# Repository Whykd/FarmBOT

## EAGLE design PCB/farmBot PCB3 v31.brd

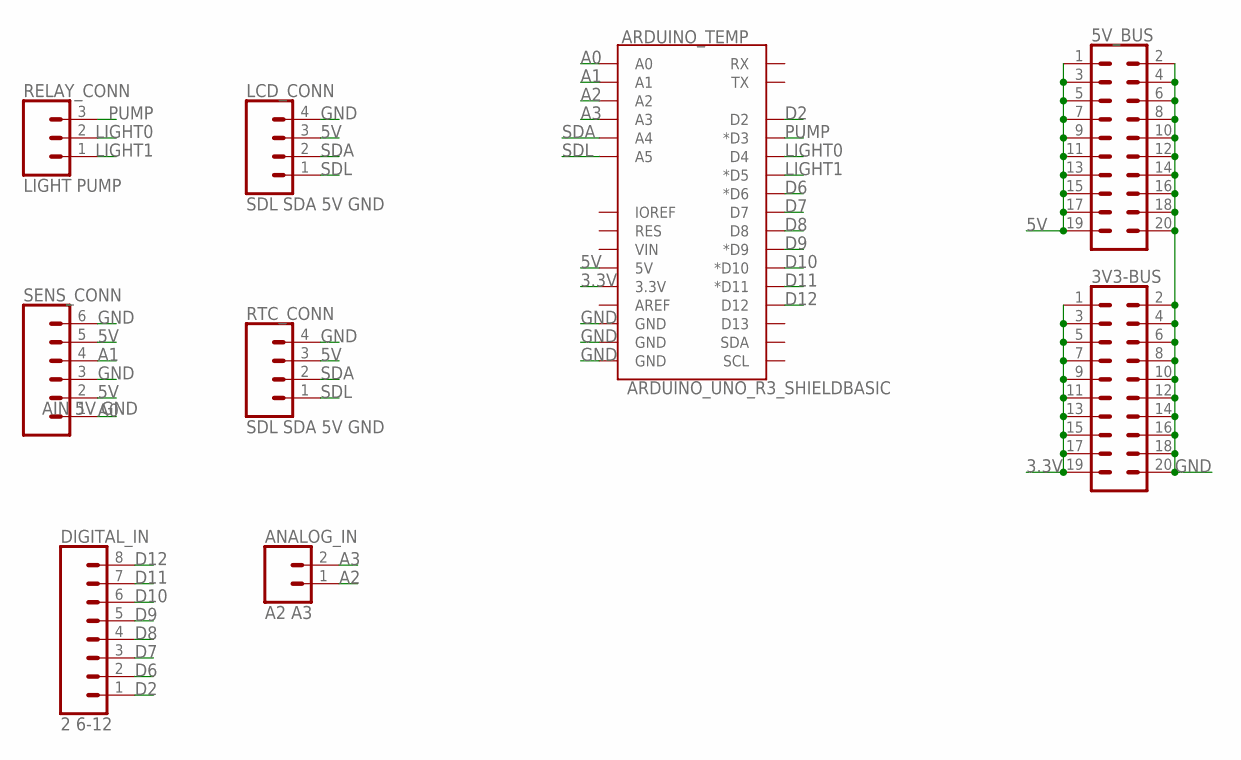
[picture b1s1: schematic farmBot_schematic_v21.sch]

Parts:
3V3-BUS, 5V_BUS: CONN_10X2; 2X10
ANALOG_IN: A2 A3; 1X02
ARDUINO_TEMP: ARDUINO_UNO_R3_SHIELDBASIC; UNO_R3_SHIELD
DIGITAL_IN: 2 6-12; 1X08
LCD_CONN: SDL SDA 5V GND; 1X04
RELAY_CONN: LIGHT PUMP; 1X03
RTC_CONN: SDL SDA 5V GND; 1X04
SENS_CONN: AIN 5V GND; 1X06

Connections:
3.3V: 3V3-BUS.1, 3V3-BUS.3, 3V3-BUS.5, 3V3-BUS.7, 3V3-BUS.9, 3V3-BUS.11, 3V3-BUS.13, 3V3-BUS.15, 3V3-BUS.17, 3V3-BUS.19, ARDUINO_TEMP.3.3V
5V: 5V_BUS.1, 5V_BUS.3, 5V_BUS.5, 5V_BUS.7, 5V_BUS.9, 5V_BUS.11, 5V_BUS.13, 5V_BUS.15, 5V_BUS.17, 5V_BUS.19, ARDUINO_TEMP.5V, LCD_CONN.3, RTC_CONN.3, SENS_CONN.2, SENS_CONN.5
A0: ARDUINO_TEMP.A0, SENS_CONN.1
A1: ARDUINO_TEMP.A1, SENS_CONN.4
A2: ANALOG_IN.1, ARDUINO_TEMP.A2
A3: ANALOG_IN.2, ARDUINO_TEMP.A3
D2: ARDUINO_TEMP.D2, DIGITAL_IN.1
D6: ARDUINO_TEMP.D6 (*D6), DIGITAL_IN.2
D7: ARDUINO_TEMP.D7, DIGITAL_IN.3
D8: ARDUINO_TEMP.D8, DIGITAL_IN.4
D9: ARDUINO_TEMP.D9 (*D9), DIGITAL_IN.5
D10: ARDUINO_TEMP.D10 (*D10), DIGITAL_IN.6
D11: ARDUINO_TEMP.D11 (*D11), DIGITAL_IN.7
D12: ARDUINO_TEMP.D12, DIGITAL_IN.8
GND: 3V3-BUS.2, 3V3-BUS.4, 3V3-BUS.6, 3V3-BUS.8, 3V3-BUS.10, 3V3-BUS.12, 3V3-BUS.14, 3V3-BUS.16, 3V3-BUS.18, 3V3-BUS.20, 5V_BUS.2, 5V_BUS.4, 5V_BUS.6, 5V_BUS.8, 5V_BUS.10, 5V_BUS.12, 5V_BUS.14, 5V_BUS.16, 5V_BUS.18, 5V_BUS.20, ARDUINO_TEMP.GND@0 (GND), ARDUINO_TEMP.GND@1 (GND), ARDUINO_TEMP.GND@2 (GND), LCD_CONN.4, RTC_CONN.4, SENS_CONN.3, SENS_CONN.6
LIGHT0: ARDUINO_TEMP.D4, RELAY_CONN.2
LIGHT1: ARDUINO_TEMP.D5 (*D5), RELAY_CONN.1
PUMP: ARDUINO_TEMP.D3 (*D3), RELAY_CONN.3
SDA: ARDUINO_TEMP.A4, LCD_CONN.2, RTC_CONN.2
SDL: ARDUINO_TEMP.A5, LCD_CONN.1, RTC_CONN.1

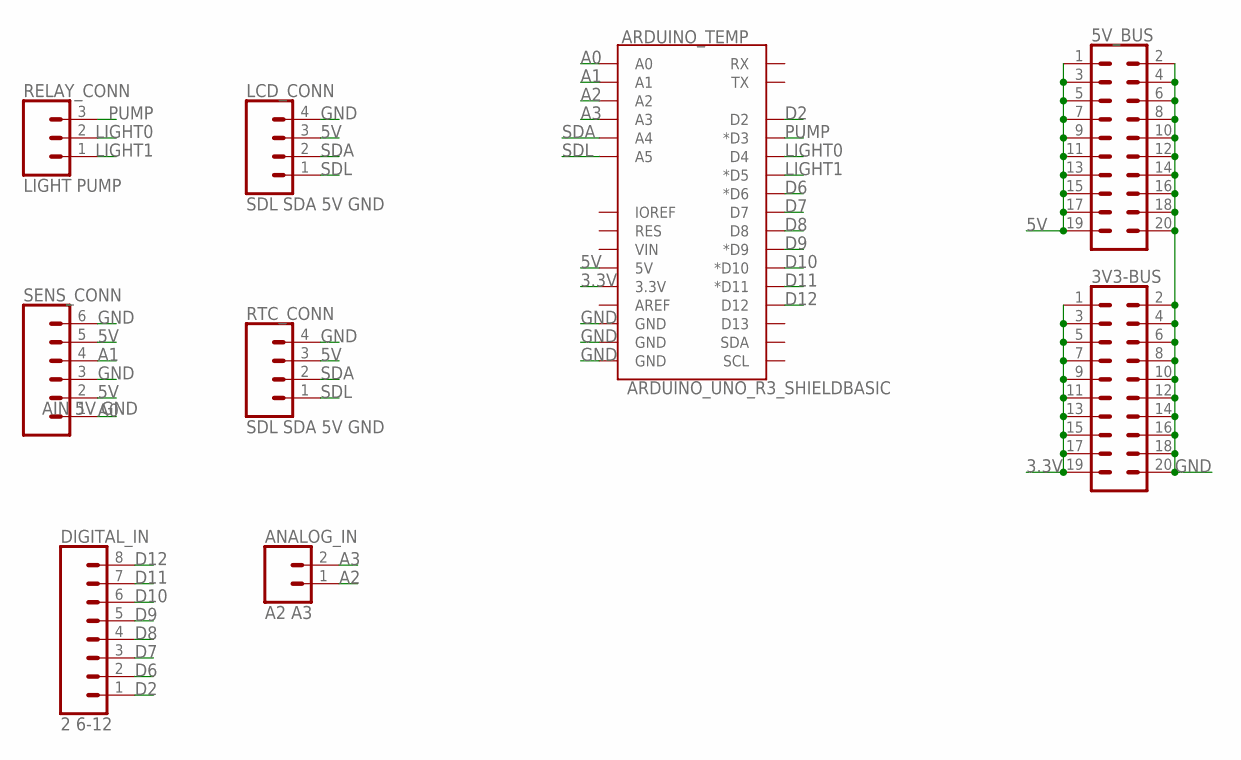
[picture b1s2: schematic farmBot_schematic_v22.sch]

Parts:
3V3-BUS, 5V_BUS: CONN_10X2; 2X10
ANALOG_IN: A2 A3; 1X02
ARDUINO_TEMP: ARDUINO_UNO_R3_SHIELDBASIC; UNO_R3_SHIELD
DIGITAL_IN: 2 6-12; 1X08
LCD_CONN: SDL SDA 5V GND; 1X04
RELAY_CONN: LIGHT PUMP; 1X03
RTC_CONN: SDL SDA 5V GND; 1X04
SENS_CONN: AIN 5V GND; 1X06

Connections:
3.3V: 3V3-BUS.1, 3V3-BUS.3, 3V3-BUS.5, 3V3-BUS.7, 3V3-BUS.9, 3V3-BUS.11, 3V3-BUS.13, 3V3-BUS.15, 3V3-BUS.17, 3V3-BUS.19, ARDUINO_TEMP.3.3V
5V: 5V_BUS.1, 5V_BUS.3, 5V_BUS.5, 5V_BUS.7, 5V_BUS.9, 5V_BUS.11, 5V_BUS.13, 5V_BUS.15, 5V_BUS.17, 5V_BUS.19, ARDUINO_TEMP.5V, LCD_CONN.3, RTC_CONN.3, SENS_CONN.2, SENS_CONN.5
A0: ARDUINO_TEMP.A0, SENS_CONN.1
A1: ARDUINO_TEMP.A1, SENS_CONN.4
A2: ANALOG_IN.1, ARDUINO_TEMP.A2
A3: ANALOG_IN.2, ARDUINO_TEMP.A3
D2: ARDUINO_TEMP.D2, DIGITAL_IN.1
D6: ARDUINO_TEMP.D6 (*D6), DIGITAL_IN.2
D7: ARDUINO_TEMP.D7, DIGITAL_IN.3
D8: ARDUINO_TEMP.D8, DIGITAL_IN.4
D9: ARDUINO_TEMP.D9 (*D9), DIGITAL_IN.5
D10: ARDUINO_TEMP.D10 (*D10), DIGITAL_IN.6
D11: ARDUINO_TEMP.D11 (*D11), DIGITAL_IN.7
D12: ARDUINO_TEMP.D12, DIGITAL_IN.8
GND: 3V3-BUS.2, 3V3-BUS.4, 3V3-BUS.6, 3V3-BUS.8, 3V3-BUS.10, 3V3-BUS.12, 3V3-BUS.14, 3V3-BUS.16, 3V3-BUS.18, 3V3-BUS.20, 5V_BUS.2, 5V_BUS.4, 5V_BUS.6, 5V_BUS.8, 5V_BUS.10, 5V_BUS.12, 5V_BUS.14, 5V_BUS.16, 5V_BUS.18, 5V_BUS.20, ARDUINO_TEMP.GND@0 (GND), ARDUINO_TEMP.GND@1 (GND), ARDUINO_TEMP.GND@2 (GND), LCD_CONN.4, RTC_CONN.4, SENS_CONN.3, SENS_CONN.6
LIGHT0: ARDUINO_TEMP.D4, RELAY_CONN.2
LIGHT1: ARDUINO_TEMP.D5 (*D5), RELAY_CONN.1
PUMP: ARDUINO_TEMP.D3 (*D3), RELAY_CONN.3
SDA: ARDUINO_TEMP.A4, LCD_CONN.2, RTC_CONN.2
SDL: ARDUINO_TEMP.A5, LCD_CONN.1, RTC_CONN.1

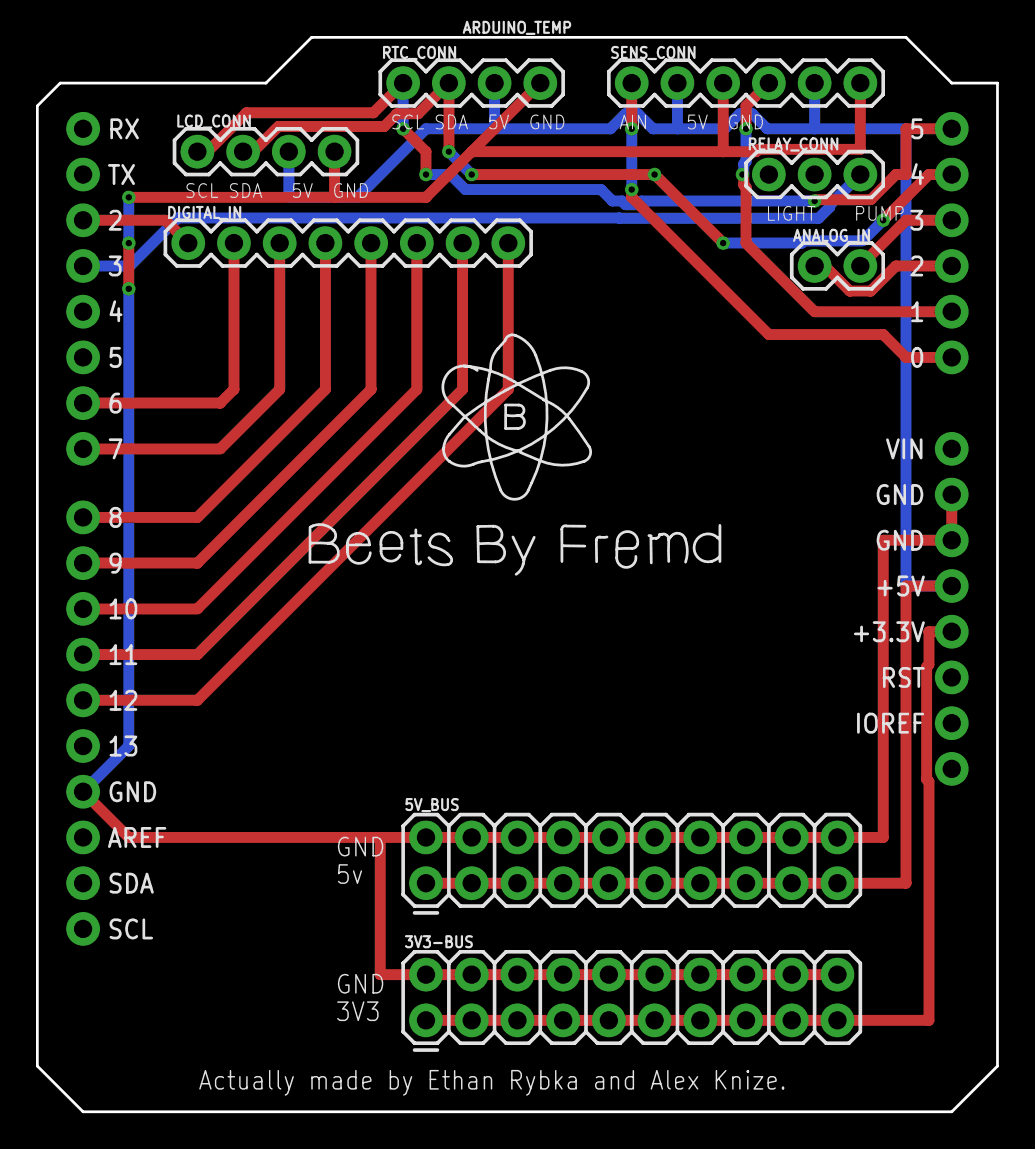
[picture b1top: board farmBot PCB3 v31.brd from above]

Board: 2 copper layers, 53.3 x 59.7 mm, 9 parts (0 on the bottom side), 20 nets.

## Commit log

2022-10-03 Initial Commit
    Added all files
2022-10-12 code
2022-10-12 comment
2022-10-12 updated code
2022-11-07 fixed issues
2022-11-10 change
2022-12-01 new pcb
2022-12-06 update silkscreen
2022-12-26 fixed format
2023-02-07 IT WORKIE
2023-02-21 final
2023-02-21 final?
2023-02-22 Initial WebUI
2023-02-25 API and WebUI update
2023-02-26 Data Modification Update (UNTESTED)
2023-02-26 fixed global var issue
2023-02-27 Database Stuff and Small Fixes
2023-02-27 fixed problems
    need to fix checkUpdates()
2023-03-04 fix api ish
2023-03-06 Shell Script Automation Time
2023-03-07 Spelling Problem Fix
2023-03-07 ports + more stuff
2023-03-22 fixed checkupdates
2023-04-04 graph workie
2023-04-06 fix live view
2023-04-08 hell incarnate
2023-04-11 fix?
2023-04-19 More Data
2023-04-22 Pain and Clocks
2023-04-26 fix rtc set time
2023-05-02 Possible Data Dropout Fix
2023-05-12 jank
2023-05-15 fixed prod
    shouldnt have pushed on a friday
2023-06-27 comments
2023-07-22 Start of the move to Json over serial
2023-09-07 change timings
2023-09-12 jank?
2023-09-14 Move to JSON
2023-09-18 Add display running
2023-09-20 update file to match pi
2023-09-22 can show nice graphs
2023-09-25 display node test
2023-09-25 More displays stuff
2023-09-27 might work
2023-09-29 added comment
2023-10-02 possible fix
2023-10-13 maybe work
2023-10-16 will use to test if it makes it here
2023-10-16 maybe it work?
2023-10-30 Changed back to having 2 files
2023-11-14 Minimal Version 1.0.0
2023-11-14 v1.0.0
2023-11-14 v2 start

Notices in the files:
parts and their libraries:
SparkFun-Connectors: Licensing: Creative Commons ShareAlike 4.0 International - https://creativecommons.org/licenses/by-sa/4.0
